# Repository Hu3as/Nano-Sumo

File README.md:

## <div align="center">Nano sumo fighting robots</div>

 <div align="center">
A robot designed and built as an interactive showcase for a student research group. The set includes two robots in different colors, programmed to detect their opponent using sensors and push them out of the play area. The arena is defined by a special mat or a highly visible tape.
The project is built using three custom-designed PCBs that I developed. These boards integrate a battery management system, an STM32 microcontroller, an LED with a control button, a motor driver, two micro motors, and four optical sensors that detect both the opponent’s position and the boundary lines of the play area.
 </div>

<div align="center">

</div>

### Below are images of the PCB and schematics of the individual modules.

### Schematics

### All files are available in repository.

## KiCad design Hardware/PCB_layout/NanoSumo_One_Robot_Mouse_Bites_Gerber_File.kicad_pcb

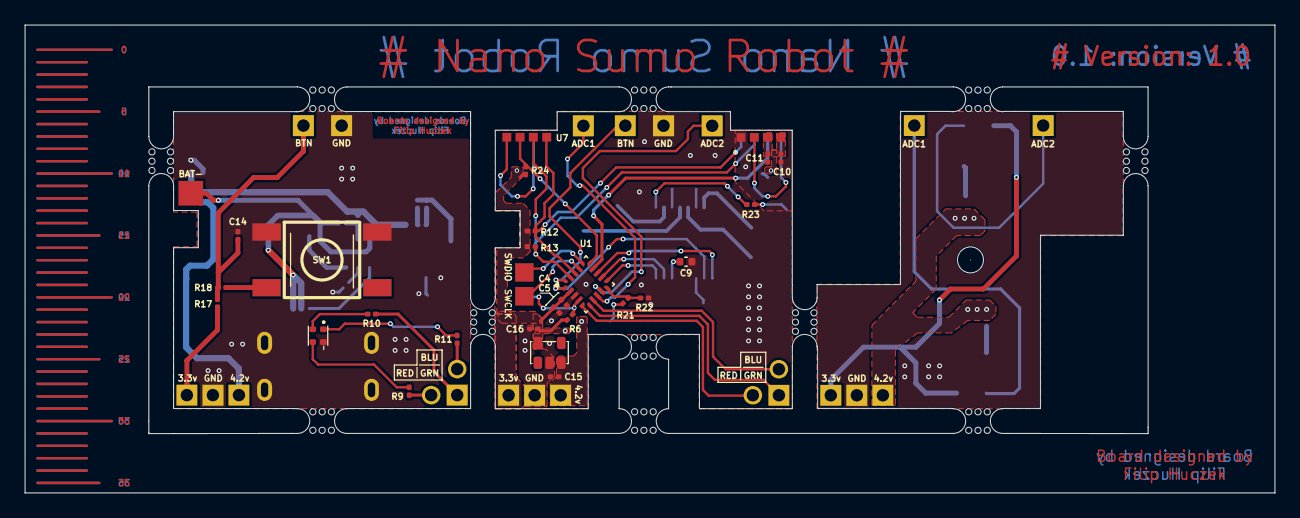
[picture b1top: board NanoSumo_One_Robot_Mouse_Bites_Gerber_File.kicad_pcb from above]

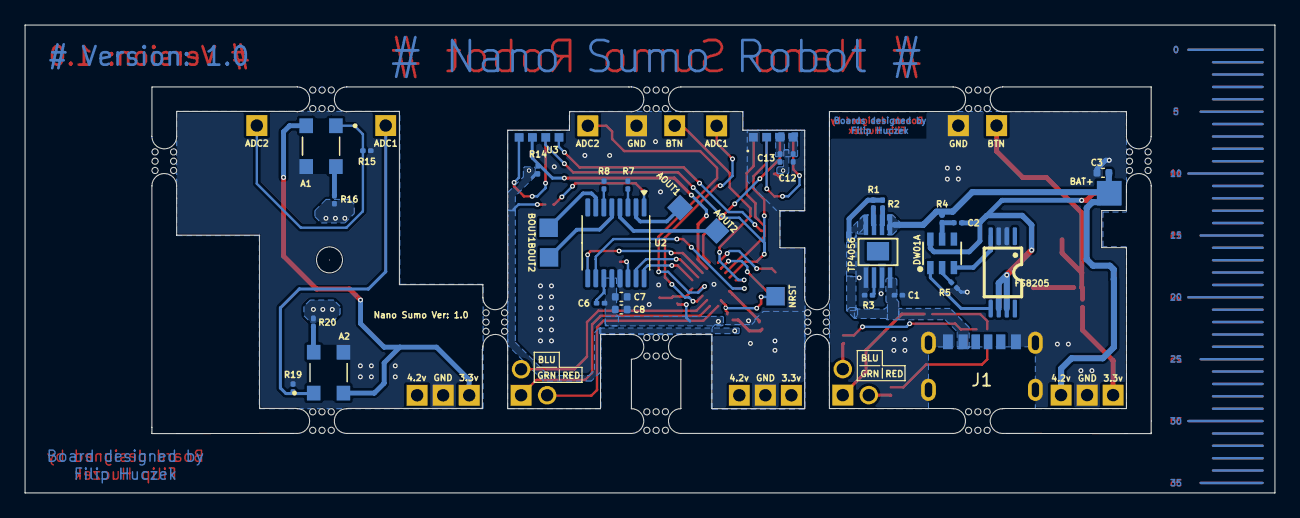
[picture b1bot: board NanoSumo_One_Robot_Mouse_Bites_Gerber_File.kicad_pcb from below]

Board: 2 copper layers, 101.0 x 37.8 mm, 73 parts (34 on the bottom side), 47 nets.

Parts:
A1, A2: GP2S700HCP; XDCR_GP2S700HCP
AOUT1: DC_Motor_1+; Pad
AOUT2: DC_Motor_1-; Pad
BAT+: Battery+; Pad
BAT-: Battery-; Pad
BOUT1: DC_Motor_2+; Pad
BOUT2: DC_Motor_2-; Pad
C1, C2, C5, C6, C10, C12, C14: 100nF; C_0201_0603Metric
C3, C7, C8, C9: 10uF; C_0402_1005Metric
C4, C15, C16: 10nF; C_0201_0603Metric
C11, C13: 2.2uF; C_0201_0603Metric
J1: USB4125-GF-A-0190_REVA2; GCT_USB4125-GF-A-0190_REVA2
LED1: XZM2CRKM2DGFBB45SCCB; LED_RGB_NanoSumo
NRST: NRST; Pad
R1, R2, R5: 1k; R_0201_0603Metric
R3: R; R_0201_0603Metric
R4, R10, R11, R18: 100; R_0201_0603Metric
R6, R15, R17, R19, R21, R22: 10k; R_0201_0603Metric
R7, R8: 200; R_0201_0603Metric
R9: 60-80; R_0201_0603Metric
R12, R13: 2.2k; R_0201_0603Metric
R14, R24: 8.2k; R_0201_0603Metric
R16, R20: 150; R_0201_0603Metric
R23: 30k; R_0201_0603Metric
SW1: SW_Push; tactile_Switch
SWCLK: SWCLK; Pad
SWDIO: SWDIO; Pad
U1: STM32C011F4Ux; ST_UFQFPN-20_3x3mm_P0.5mm
U2: DRV8833PW; TSSOP-16_4.4x5mm_P0.65mm
U3, U7: VCNL4040M3OE; VISHAY_VCNL4040_4X2X1.1
U4: Li-Pol Charger; TP4056
U6: DW01A
U8: DS9078-20
U9: NM8205A
mouse-bite-2mm-slot, mouse-bite-2mm-slot#2, mouse-bite-2mm-slot#3, mouse-bite-2mm-slot#4, mouse-bite-2mm-slot#5, mouse-bite-2mm-slot#6, mouse-bite-2mm-slot#7, mouse-bite-2mm-slot#8, mouse-bite-2mm-slot#9, mouse-bite-2mm-slot#10, mouse-bite-2mm-slot#11: VAL**; mouse-bite-2mm-slot

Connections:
+3.3V: A1.2 (C), A2.2 (C), C4.2, C5.2, C10.2, C11.2, C12.2, C13.2, C16.2, R6.2, R12.2, R13.2, R14.2, R17.1, R23.1, R24.2, U1.2 (VDD), U3.3, U3.4, U7.3, U7.4, U8.5 (VOUT)
+4.2V BAT: BAT+.1, C3.1, C6.1, C7.1, C8.1, C15.1, R4.2, R16.2, R20.2, R21.2, U2.12 (VM), U4.5 (BAT), U8.1 (Vin), U8.3 (EN)
+5V: C1.1, J1.A9 (VBUS), J1.B9 (VBUS__1), R1.1, R2.1, U4.4 (VCC), U4.8 (CE)
ADC_1: A2.1 (E), R19.2, U1.8 (PA3)
ADC_2: A1.1 (E), R15.2, U1.9 (PA4)
Ain1: U1.11 (PA6), U2.16 (AIN1)
Ain2: U1.12 (PA7), U2.15 (AIN2)
BatteryVoltage_ADC: R21.1, R22.2, U1.10 (PA5)
Bin1: U1.13 (PA8), U2.9 (BIN1)
Bin2: U1.1 (PC15), U2.10 (BIN2)
Button: C14.2, R17.2, R18.1, U1.20 (PC14)
GND: A1.3 (CA), A2.3 (CA), C1.2, C3.2, C4.1, C5.1, C7.2, C8.2, C9.2, C10.1, C11.1, C12.1, C13.1, C14.1, C15.2, C16.1, J1.A12 (GND), J1.B12 (GND__1), J1.S1 (SHIELD), J1.S2 (SHIELD__1), J1.S3 (SHIELD__2), J1.S4 (SHIELD__3), LED1.4, R3.1, R5.1, R7.1, R8.1, R15.1, R19.1, R22.1, SW1.2, U1.3 (VSS), U2.13 (GND), U3.1, U4.1 (TEMP), U4.3 (GND), U7.1, U8.2 (GND), U9.2 (S1), U9.3 (S1)
INTERRUPT_1: R14.1, U1.14 (PA9/PA11), U3.6
INTERRUPT_2: R24.1, U1.15 (PA10/PA12), U7.6
Led_B: R11.1, U1.7 (PA2)
Led_G: R10.1, U1.6 (PA1)
Led_R: R9.2, U1.5 (PA0)
NRST: NRST.1, R6.1, U1.4 (PF2)
unnamed: A1.4 (A), R16.1
unnamed: A2.4 (A), R20.1
unnamed: LED1.1, R11.2
unnamed: LED1.2, R10.2
unnamed: LED1.3, R9.1
unnamed: R18.2, SW1.1
unnamed: R7.2, U2.3 (AISEN)
unnamed: AOUT1.1, U2.2 (AOUT1)
unnamed: AOUT2.1, U2.4 (AOUT2)
unnamed: R8.2, U2.6 (BISEN)
unnamed: BOUT1.1, U2.7 (BOUT1)
unnamed: BOUT2.1, U2.5 (BOUT2)
unnamed: C6.2, U2.11 (VCP)
unnamed: C9.1, U2.14 (VINT)
unnamed: R23.2, U2.1 (~SLEEP)
unnamed: U3.2, U3.5
unnamed: R1.2, U4.7 (CHRG#)
unnamed: R3.2, U4.2 (PROG)
unnamed: R2.2, U4.6 (STDBY#)
unnamed: BAT-.1, C2.2, U6.6 (GND), U9.6 (S2), U9.7 (D2)
unnamed: U6.3 (OC), U9.4 (G1)
unnamed: U6.1 (OD), U9.5 (G2)
unnamed: C2.1, R4.1, U6.5 (VCC)
unnamed: R5.2, U6.2 (VM)
unnamed: U7.2, U7.5
SCL: R12.1, U1.18 (PB6), U3.8, U7.8
SDA: R13.1, U1.19 (PB7), U3.7, U7.7
SWCLK: SWCLK.1, U1.17 (PA14)
SWDIO: SWDIO.1, U1.16 (PA13)

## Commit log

2025-04-16 Hardware files upload
2025-04-22 Rename assembly v2.png to assembly_v2.png
2025-04-22 Rename assembly v4.png to assembly_v4.png
